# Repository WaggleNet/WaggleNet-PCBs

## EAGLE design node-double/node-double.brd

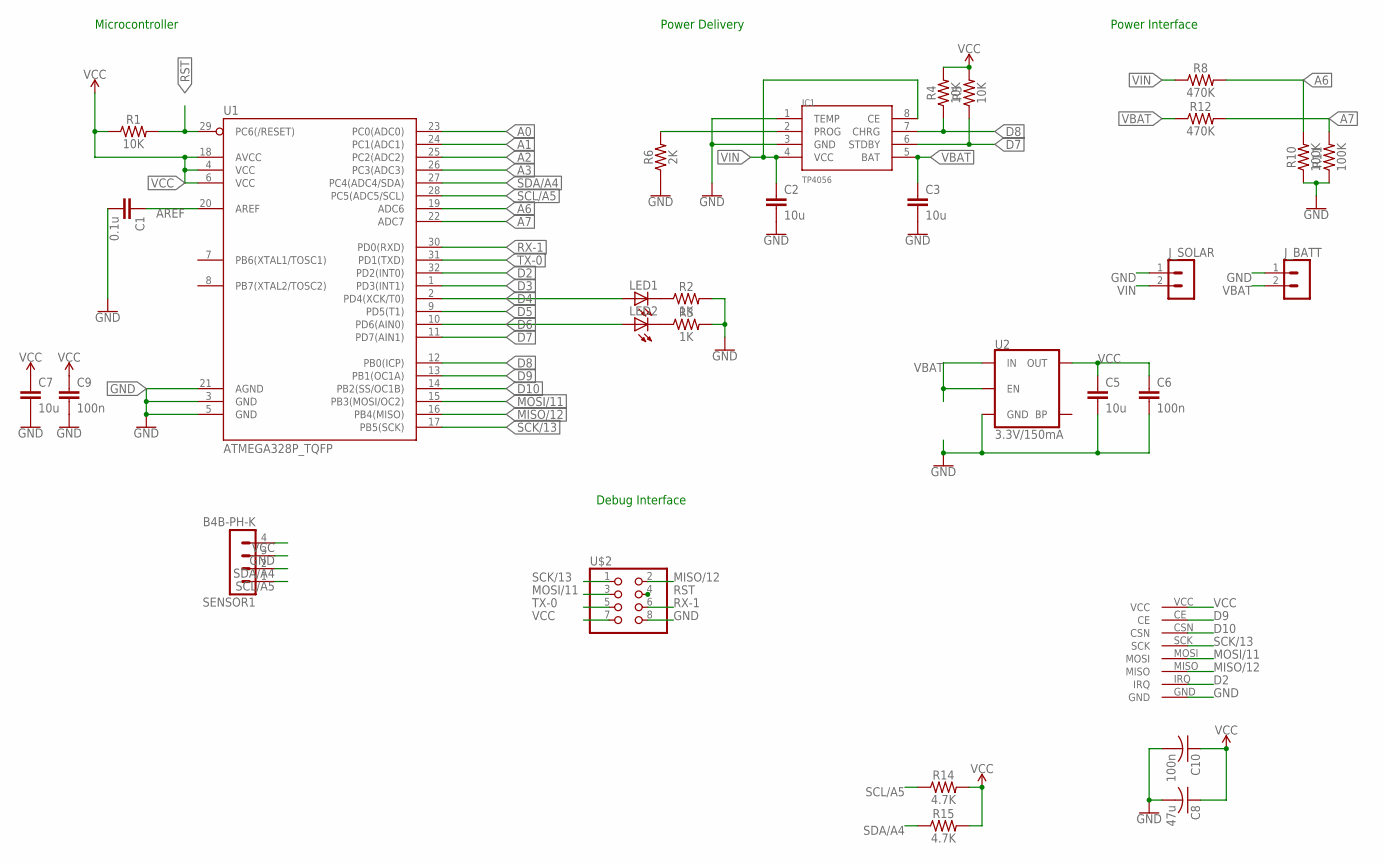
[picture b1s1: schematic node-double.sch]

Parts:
C1: 0.1u; RESC0603_L; MPN CC0603KRX7R7BB104
C2, C3, C5, C7: 10u; RESC0603_L; MPN 08056D106KAT2A
C6, C9: 100n; RESC0603_L; MPN 08056D106KAT2A
C8: 47u; C0603; MPN 08056D106KAT2A
C10: 100n; C0603; MPN 08056D106KAT2A
IC1: TP4056; SOP-8
J_BATT: B2B-PH-K
J_SOLAR: B2B-PH-K
LED1, LED2: LEDSML0805; SML0805
R1, R4, R5: 10K; 0603
R2, R3: 1K; 0603
R6: 2K; 0603; MPN CR0805-JW-222ELF
R8, R12: 470K; 0603; MPN MC01W08051330K
R10, R11: 100K; 0603; MPN CRCW0805100KFKEA
R14, R15: 4.7K; 0603; MPN RC0805JR-074K7L
SENSOR1: B4B-PH-K
U1: ATMEGA328P_TQFP; TQFP32-08; MPN ATMEGA328P-AU
U2: 3.3V/150mA; SOT23-5
U$1: ML01SSMD-SOM; ML01S
U$2: PINHD-2X4; 2X04

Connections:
A0: U1.23 (PC0(ADC0))
A1: U1.24 (PC1(ADC1))
A2: U1.25 (PC2(ADC2))
A3: U1.26 (PC3(ADC3))
A6: R8.2, R10.2, U1.19 (ADC6)
A7: R11.2, R12.2, U1.22 (ADC7)
AREF: C1.1, U1.20 (AREF)
D2: U1.32 (PD2(INT0)), U$1.IRQ
D3: U1.1 (PD3(INT1))
D4: LED1.A, U1.2 (PD4(XCK/T0))
D5: U1.9 (PD5(T1))
D6: LED2.A, U1.10 (PD6(AIN0))
D7: IC1.6 (STDBY), R5.1, U1.11 (PD7(AIN1))
D8: IC1.7 (CHRG), R4.1, U1.12 (PB0(ICP))
D9: U1.13 (PB1(OC1A)), U$1.CE
D10: U1.14 (PB2(SS/OC1B)), U$1.CSN
GND: C1.2, C2.2, C3.2, C5.2, C6.2, C7.2, C8.2, C9.2, C10.2, IC1.1 (TEMP), IC1.3 (GND), J_BATT.1, J_SOLAR.1, R2.2, R3.2, R6.1, R10.1, R11.1, SENSOR1.3, U1.3 (GND), U1.5 (GND), U1.21 (AGND), U2.2 (GND), U$1.GND, U$2.8
MISO/12: U1.16 (PB4(MISO)), U$1.MISO, U$2.2
MOSI/11: U1.15 (PB3(MOSI/OC2)), U$1.MOSI, U$2.3
unnamed: LED1.C, R2.1
unnamed: LED2.C, R3.1
PROG: IC1.2 (PROG), R6.2
RST: R1.2, U1.29 (PC6(/RESET)), U$2.4
RX-1: U1.30 (PD0(RXD)), U$2.6
SCK/13: U1.17 (PB5(SCK)), U$1.SCK, U$2.1
SCL/A5: R14.1, SENSOR1.1, U1.28 (PC5(ADC5/SCL))
SDA/A4: R15.1, SENSOR1.2, U1.27 (PC4(ADC4/SDA))
TX-0: U1.31 (PD1(TXD)), U$2.5
VBAT: C3.1, IC1.5 (BAT), J_BATT.2, R12.1, U2.1 (IN), U2.3 (EN)
VCC: C5.1, C6.1, C7.1, C8.1, C9.1, C10.1, R1.1, R4.2, R5.2, R14.2, R15.2, SENSOR1.4, U1.4 (VCC), U1.6 (VCC), U1.18 (AVCC), U2.5 (OUT), U$1.VCC, U$2.7
VIN: C2.1, IC1.4 (VCC), IC1.8 (CE), J_SOLAR.2, R8.1

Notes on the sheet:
Microcontroller
Power Delivery
Power Interface
Debug Interface

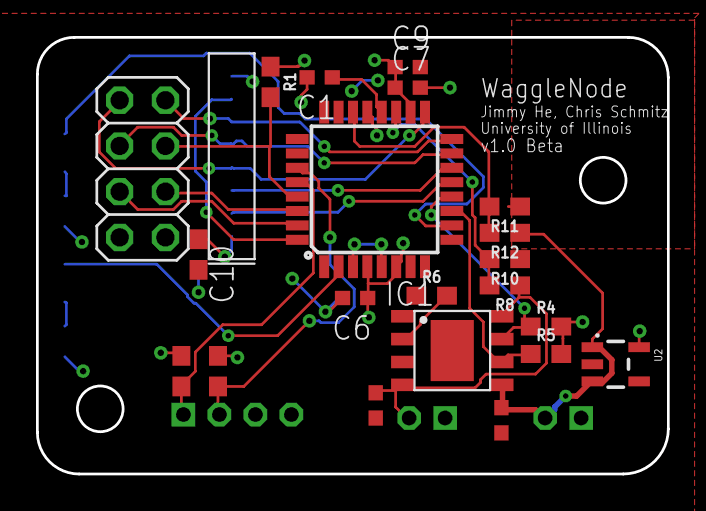
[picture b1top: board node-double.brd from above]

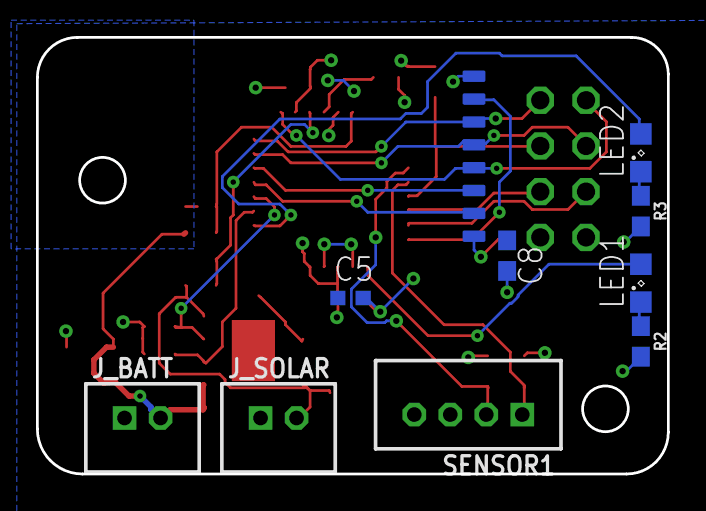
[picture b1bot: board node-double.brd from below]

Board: 2 copper layers, 35.1 x 24.3 mm, 31 parts (10 on the bottom side), 25 nets.

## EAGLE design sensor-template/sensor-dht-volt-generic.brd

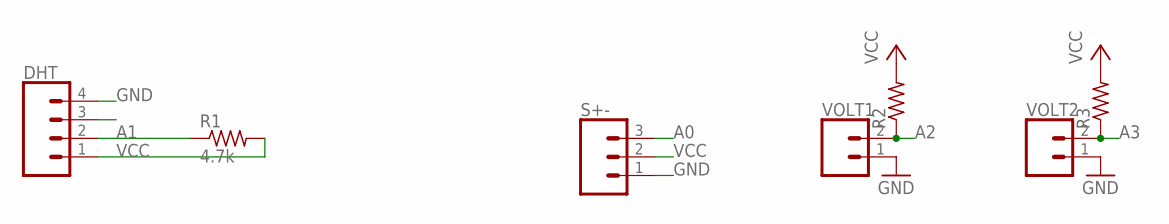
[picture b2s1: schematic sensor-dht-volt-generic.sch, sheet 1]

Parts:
DHT: CONN_04; 1X04
R1: 4.7k; R0603
R2, R3: R-US_R0603; R0603
S+-: CONN_03; 1X03
VOLT1, VOLT2: CONN_02; 1X02

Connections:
A0: S+-.3; also elsewhere on the board
A1: DHT.2, R1.1; also elsewhere on the board
A2: R2.1, VOLT1.2; also elsewhere on the board
A3: R3.1, VOLT2.2; also elsewhere on the board
GND: DHT.4, S+-.1, VOLT1.1, VOLT2.1; also elsewhere on the board
VCC: DHT.1, R1.2, R2.2, R3.2, S+-.2; also elsewhere on the board

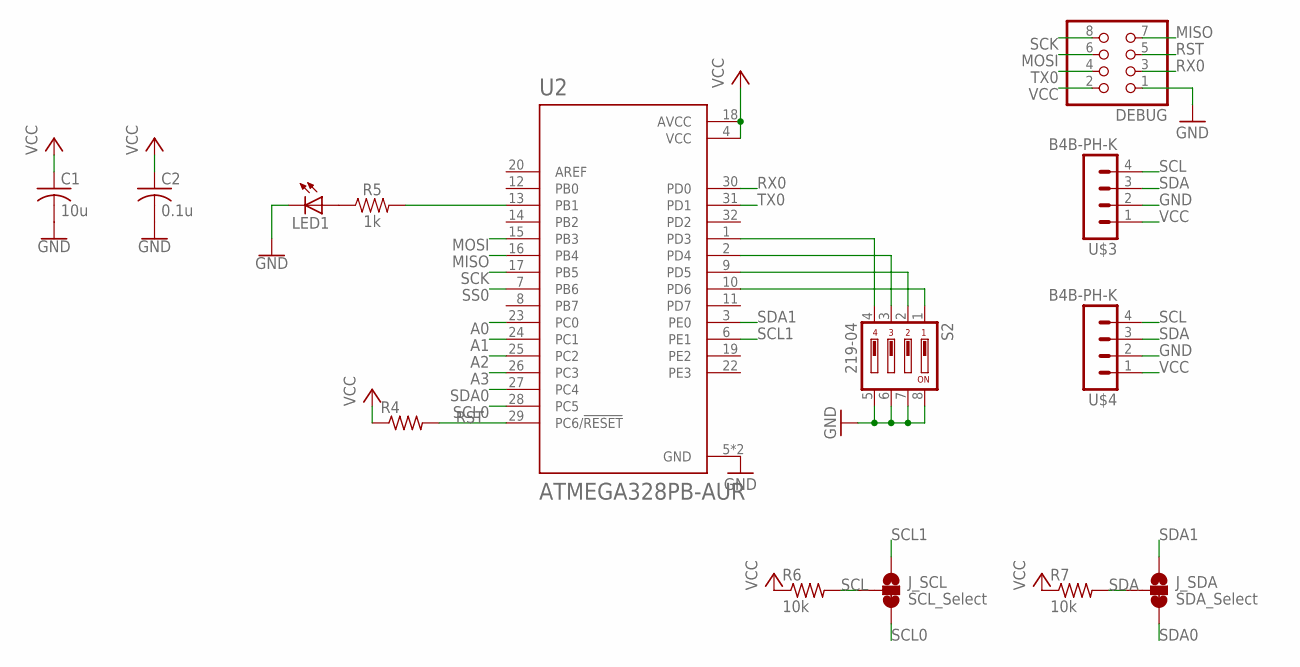
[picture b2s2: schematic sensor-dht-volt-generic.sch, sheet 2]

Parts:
C1: 10u; C0603
C2: 0.1u; C0603
DEBUG: PINHD-2X4; 2X04
J_SCL: SCL_Select; SMT-JUMPER_3_1-NC_TRACE_SILK
J_SDA: SDA_Select; SMT-JUMPER_3_1-NC_TRACE_SILK
LED1: LEDSML0805; SML0805
R4: R-US_R0603; R0603
R5: 1k; 0603
R6, R7: 10k; R0603
S2: 219-04; CTS-219-04
U2: ATMEGA328PB-AUR; QFP80P900X900X120-32N
U$3, U$4: B4B-PH-K

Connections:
A0: U2.23 (PC0); also elsewhere on the board
A1: U2.24 (PC1); also elsewhere on the board
A2: U2.25 (PC2); also elsewhere on the board
A3: U2.26 (PC3); also elsewhere on the board
GND: C1.2, C2.2, DEBUG.1, LED1.C, S2.5, S2.6, S2.7, S2.8, U2.5 (GND), U2.21 (GND), U$3.2, U$4.2; also elsewhere on the board
MISO: DEBUG.7, U2.16 (PB4)
MOSI: DEBUG.6, U2.15 (PB3)
unnamed: S2.4, U2.1 (PD3)
unnamed: S2.3, U2.2 (PD4)
unnamed: S2.2, U2.9 (PD5)
unnamed: S2.1, U2.10 (PD6)
unnamed: LED1.A, R5.1
unnamed: R5.2, U2.13 (PB1)
RST: DEBUG.5, R4.2, U2.29 (PC6/!RESET)
RX0: DEBUG.3, U2.30 (PD0)
SCK: DEBUG.8, U2.17 (PB5)
SCL: J_SCL.2, R6.2, U$3.4, U$4.4
SCL0: J_SCL.3, U2.28 (PC5)
SCL1: J_SCL.1, U2.6 (PE1)
SDA: J_SDA.2, R7.2, U$3.3, U$4.3
SDA0: J_SDA.3, U2.27 (PC4)
SDA1: J_SDA.1, U2.3 (PE0)
SS0: U2.7 (PB6)
TX0: DEBUG.4, U2.31 (PD1)
VCC: C1.1, C2.1, DEBUG.2, R4.1, R6.1, R7.1, U2.4 (VCC), U2.18 (AVCC), U$3.1, U$4.1; also elsewhere on the board

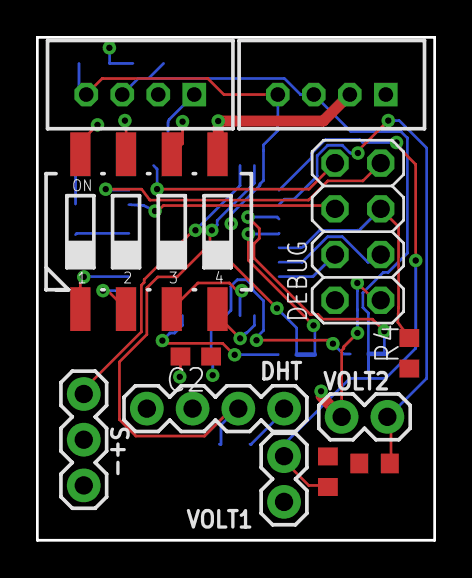
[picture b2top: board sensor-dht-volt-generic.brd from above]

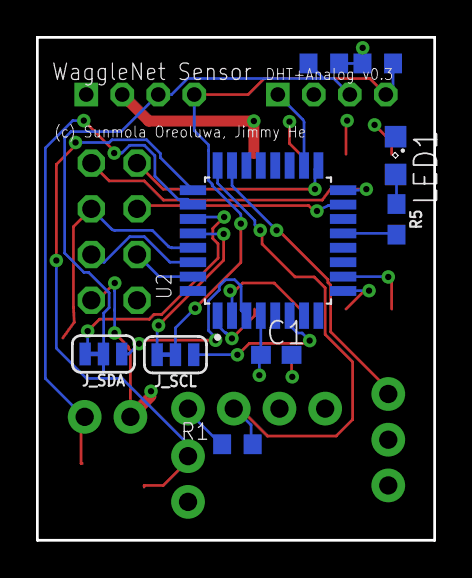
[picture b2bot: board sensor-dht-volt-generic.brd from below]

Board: 2 copper layers, 22.1 x 27.9 mm, 21 parts (9 on the bottom side), 24 nets.

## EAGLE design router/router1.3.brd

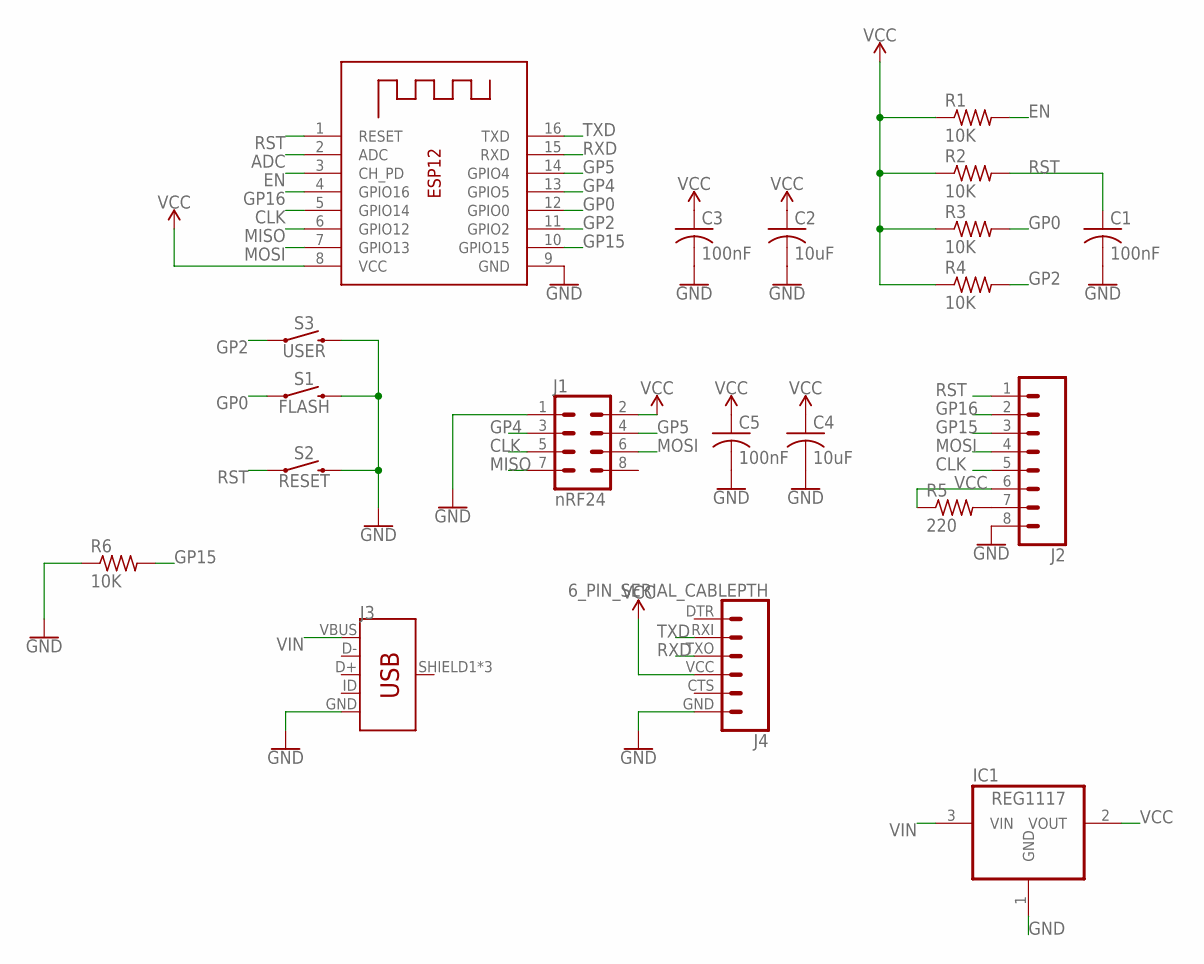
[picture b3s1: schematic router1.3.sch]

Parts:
C1, C3, C5: 100nF; C1206
C2, C4: 10uF; C1206
IC1: REG1117; SOT223
J1: nRF24; 2X4
J2: CONN_08"; 1X08
J3: USB_MICRO-B_FEMALE-SMT; USB-B-MICRO-SMD
J4: 6_PIN_SERIAL_CABLEPTH; FTDI_BASIC
R1, R2, R3, R4, R6: 10K; M1206
R5: 220; M1206
S1: FLASH; TACTILE_SWITCH_PTH_6.0MM
S2: RESET; TACTILE_SWITCH_PTH_6.0MM
S3: USER; TACTILE_SWITCH_PTH_6.0MM
X1: ESP-12

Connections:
ADC: X1.2 (ADC)
CLK: J1.5, J2.5, X1.5 (GPIO14)
EN: R1.2, X1.3 (CH_PD)
GND: C1.2, C2.2, C3.2, C4.2, C5.2, IC1.1 (GND), J1.1, J2.8, J3.GND, J4.GND (6), R6.1, S1.3 (2), S2.3 (2), S3.3 (2), X1.9 (GND)
GP0: R3.2, S1.1, X1.12 (GPIO0)
GP2: R4.2, S3.1, X1.11 (GPIO2)
GP4: J1.3, X1.13 (GPIO5)
GP5: J1.4, X1.14 (GPIO4)
GP15: J2.3, R6.2, X1.10 (GPIO15)
GP16: J2.2, X1.4 (GPIO16)
MISO: J1.7, X1.6 (GPIO12)
MOSI: J1.6, J2.4, X1.7 (GPIO13)
unnamed: J2.7, R5.2
RST: C1.1, J2.1, R2.2, S2.1, X1.1 (RESET)
RXD: J4.TXO (3), X1.15 (RXD)
TXD: J4.RXI (2), X1.16 (TXD)
VCC: C2.1, C3.1, C4.1, C5.1, IC1.2 (VOUT), J1.2, J2.6, J4.VCC (4), R1.1, R2.1, R3.1, R4.1, R5.1, X1.8 (VCC)
VIN: IC1.3 (VIN), J3.VBUS

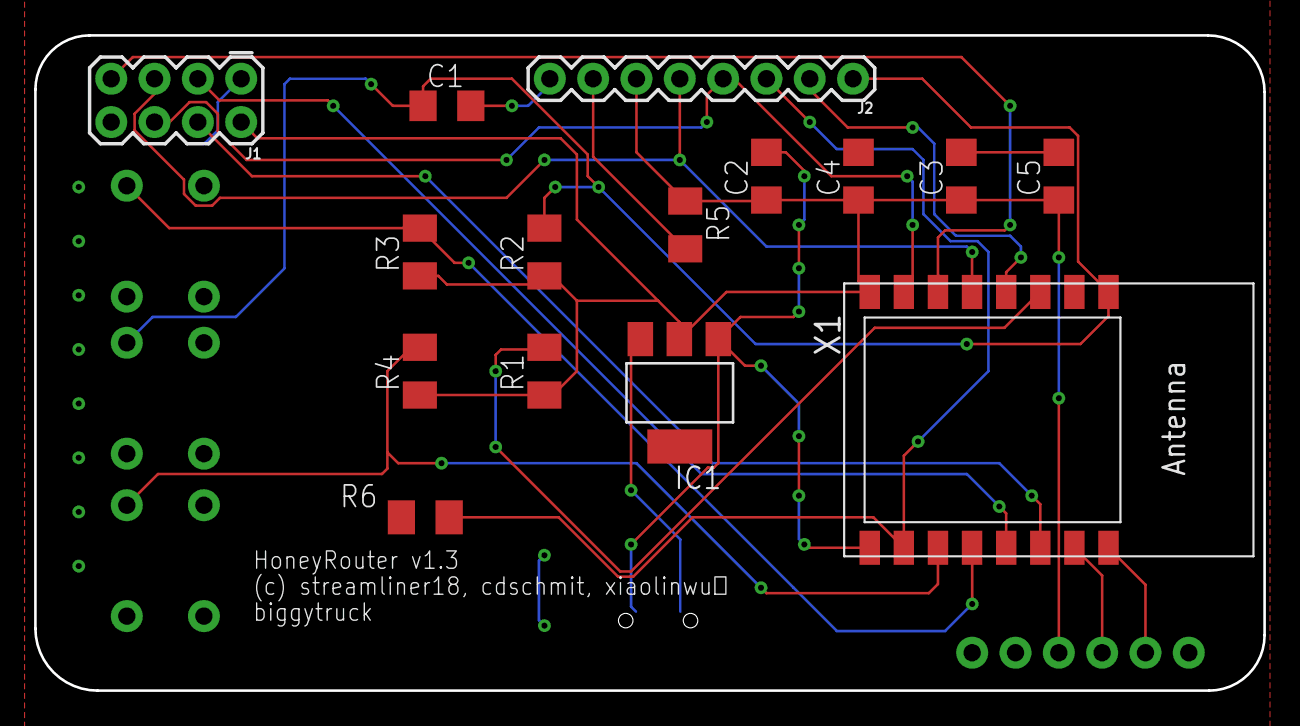
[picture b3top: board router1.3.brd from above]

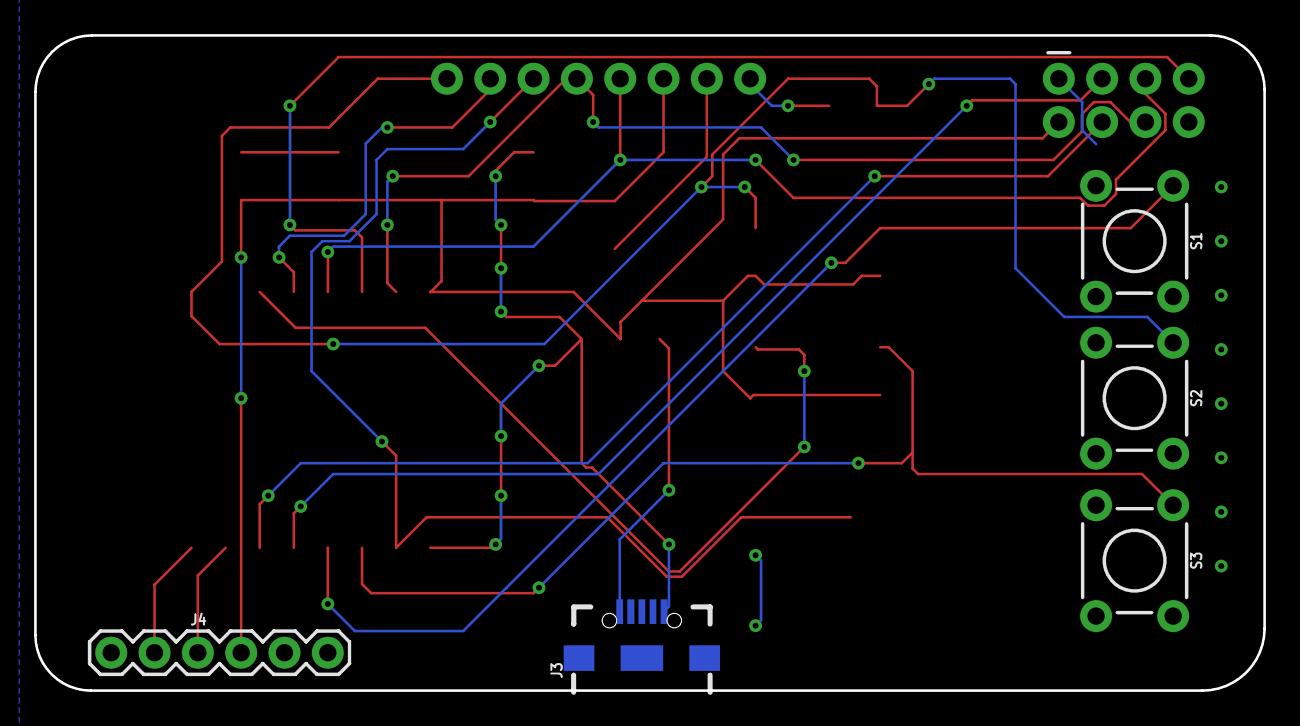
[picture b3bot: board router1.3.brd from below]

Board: 2 copper layers, 72.1 x 38.4 mm, 20 parts (5 on the bottom side), 17 nets.

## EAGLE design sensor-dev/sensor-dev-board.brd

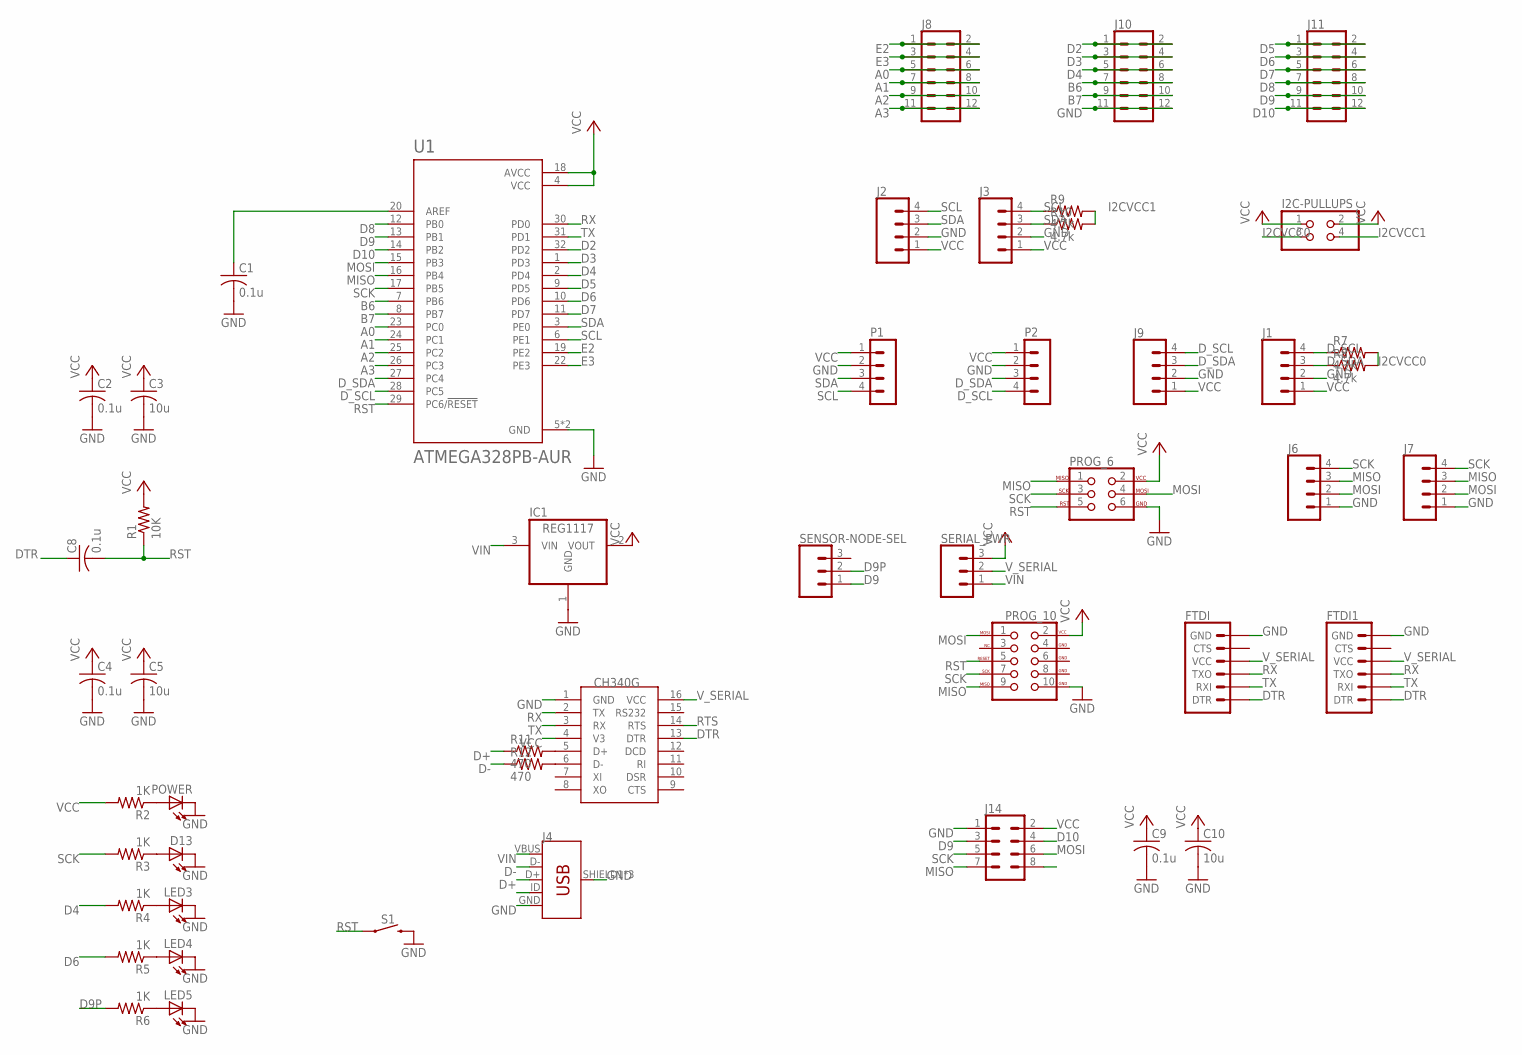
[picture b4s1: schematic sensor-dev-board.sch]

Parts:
C1, C2, C4, C8, C9: 0.1u; C1206
C3, C5, C10: 10u; C1206
CH340C: CH340C; SOIC16
D13: LEDSML1206; SML1206
FTDI, FTDI1: 6_PIN_SERIAL_TARGET; 1X06
I2C-PULLUPS: PINHD-2X2; 2X02
IC1: REG1117; SOT223
J1, J2, J3, J6, J7, J9: CONN_04; 1X04
J4: USB_MICRO-B_FEMALE-SMT; USB-B-MICRO-SMD
J8, J10, J11: CONN_06X2PTH_FEMALE; 2X6
J14: CONN_04X2; 2X4
LED3, LED4, LED5: LEDSML1206; SML1206
P1, P2: B4B-PH-K
POWER: LEDSML1206; SML1206
PROG_6: AVR_SPI_PROG_3X2PTH; 2X3
PROG_10: AVR_SPI_PROG_5X2PTH; 2X5
R1: 10K; R1206
R2, R3, R4, R5, R6: 1K; R1206
R7, R8, R9, R10: 4.7k; R1206
R11, R12: 470; R1206
S1: MOMENTARY-SWITCH-SPST-PTH-6.0MM; TACTILE_SWITCH_PTH_6.0MM
SENSOR-NODE-SEL: CONN_03; 1X03
SERIAL_PWR: CONN_03; 1X03
U1: ATMEGA328PB-AUR; QFP80P900X900X120-32N

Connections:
A0: J8.5, J8.6, U1.23 (PC0)
A1: J8.7, J8.8, U1.24 (PC1)
A2: J8.9, J8.10, U1.25 (PC2)
A3: J8.11, J8.12, U1.26 (PC3)
B6: J10.7, J10.8, U1.7 (PB6)
B7: J10.9, J10.10, U1.8 (PB7)
D2: J10.1, J10.2, U1.32 (PD2)
D3: J10.3, J10.4, U1.1 (PD3)
D4: J10.5, J10.6, R4.2, U1.2 (PD4)
D5: J11.1, J11.2, U1.9 (PD5)
D6: J11.3, J11.4, R5.2, U1.10 (PD6)
D7: J11.5, J11.6, U1.11 (PD7)
D8: J11.7, J11.8, U1.12 (PB0)
D9: J11.9, J11.10, J14.3, SENSOR-NODE-SEL.1, U1.13 (PB1)
D9P: R6.2, SENSOR-NODE-SEL.2
D10: J11.11, J11.12, J14.4, U1.14 (PB2)
D+: J4.D+, R11.1
D-: J4.D-, R12.1
DTR: C8.1, CH340C.13 (DTR), FTDI.1 (DTR), FTDI1.1 (DTR)
D_SCL: J1.4, J9.4, P2.4, R7.1, U1.28 (PC5)
D_SDA: J1.3, J9.3, P2.3, R8.1, U1.27 (PC4)
E2: J8.1, J8.2, U1.19 (PE2)
E3: J8.3, J8.4, U1.22 (PE3)
GND: C1.2, C2.2, C3.2, C4.2, C5.2, C9.2, C10.2, CH340C.1 (GND), D13.C, FTDI.6 (GND), FTDI1.6 (GND), IC1.1 (GND), J1.2, J2.2, J3.2, J4.GND, J4.SHIELD1 (SHIELD), J4.SHIELD2 (SHIELD), J4.SHIELD3 (SHIELD), J6.1, J7.1, J9.2, J10.11, J10.12, J14.1, LED3.C, LED4.C, LED5.C, P1.2, P2.2, POWER.C, PROG_6.6, PROG_10.4 (GND), PROG_10.6 (GND), PROG_10.8 (GND), PROG_10.10 (GND), S1.3 (2), U1.5 (GND), U1.21 (GND)
I2CVCC0: I2C-PULLUPS.3, R7.2, R8.2
I2CVCC1: I2C-PULLUPS.4, R9.2, R10.2
MISO: J6.3, J7.3, J14.7, PROG_6.1, PROG_10.9 (MISO), U1.16 (PB4)
MOSI: J6.2, J7.2, J14.6, PROG_6.4, PROG_10.1 (MOSI), U1.15 (PB3)
unnamed: CH340C.5 (D+), R11.2
unnamed: CH340C.6 (D-), R12.2
unnamed: C1.1, U1.20 (AREF)
unnamed: POWER.A, R2.1
unnamed: D13.A, R3.1
unnamed: LED3.A, R4.1
unnamed: LED4.A, R5.1
unnamed: LED5.A, R6.1
RST: C8.2, PROG_6.5, PROG_10.5 (RESET), R1.1, S1.1, U1.29 (PC6/!RESET)
RTS: CH340C.14 (RTS)
RX: CH340C.2 (TX), FTDI.3 (TXO), FTDI1.3 (TXO), U1.30 (PD0)
SCK: J6.4, J7.4, J14.5, PROG_6.3, PROG_10.7 (SCK), R3.2, U1.17 (PB5)
SCL: J2.4, J3.4, P1.4, R9.1, U1.6 (PE1)
SDA: J2.3, J3.3, P1.3, R10.1, U1.3 (PE0)
TX: CH340C.3 (RX), FTDI.2 (RXI), FTDI1.2 (RXI), U1.31 (PD1)
VCC: C2.1, C3.1, C4.1, C5.1, C9.1, C10.1, CH340C.4 (V3), I2C-PULLUPS.1, I2C-PULLUPS.2, IC1.2 (VOUT), J1.1, J2.1, J3.1, J9.1, J14.2, P1.1, P2.1, PROG_6.2, PROG_10.2 (VCC), R1.2, R2.2, SERIAL_PWR.3, U1.4 (VCC), U1.18 (AVCC)
VIN: IC1.3 (VIN), J4.VBUS, SERIAL_PWR.1
V_SERIAL: CH340C.16 (VCC), FTDI.4 (VCC), FTDI1.4 (VCC), SERIAL_PWR.2

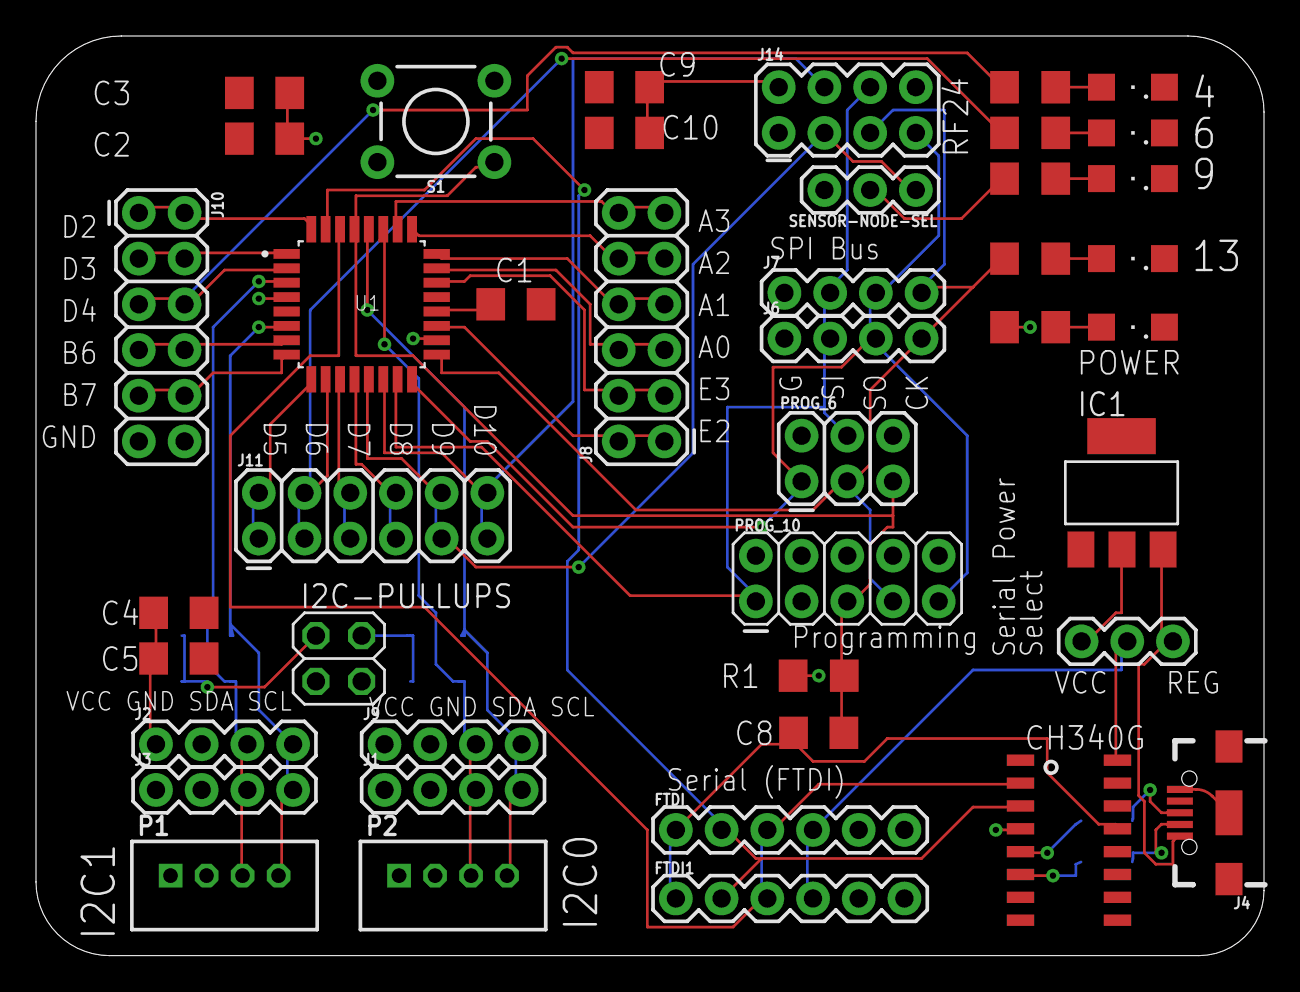
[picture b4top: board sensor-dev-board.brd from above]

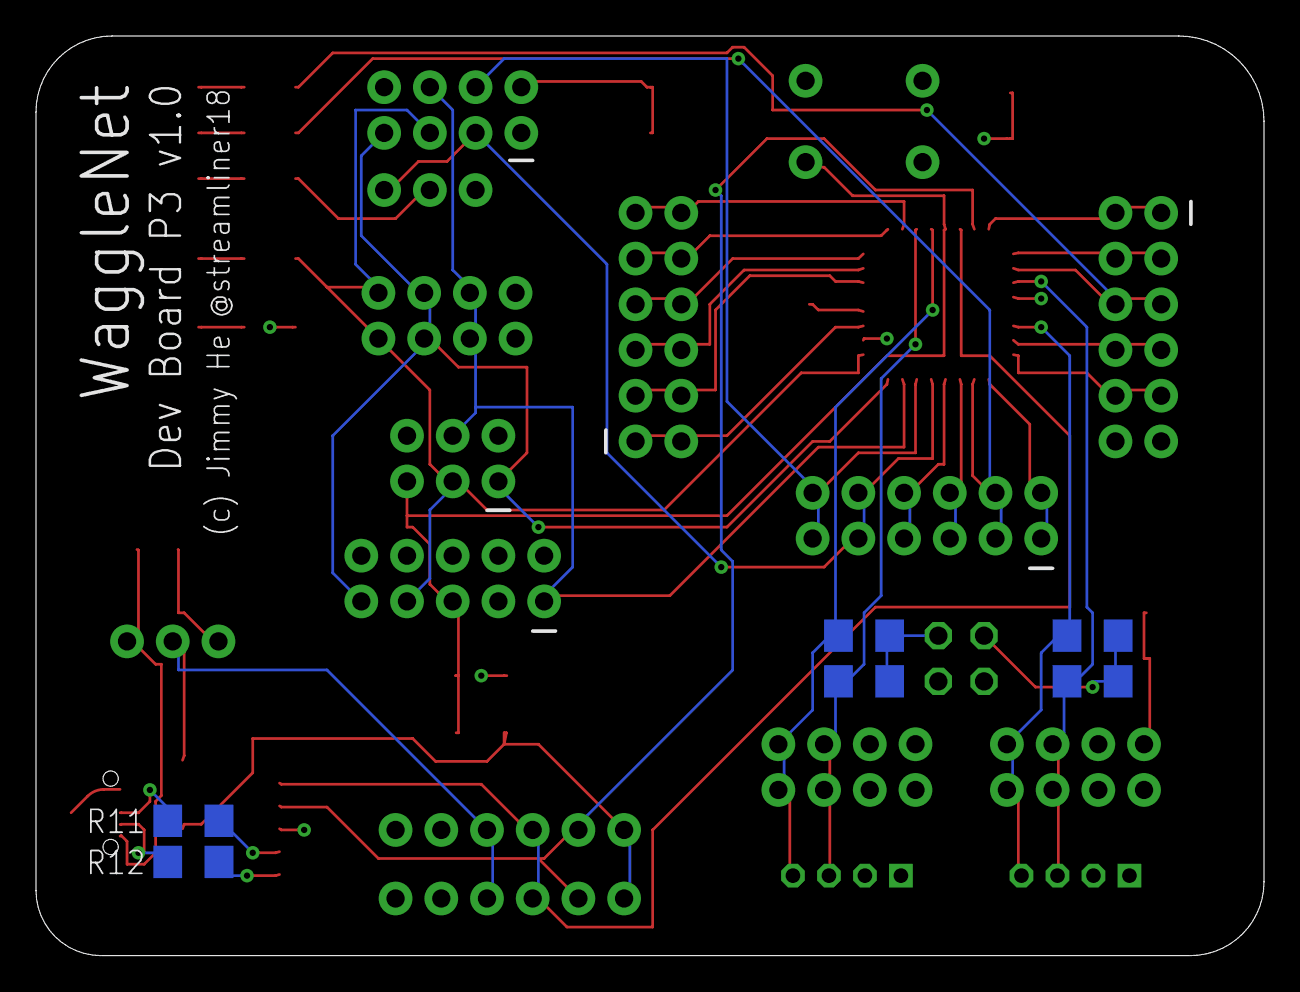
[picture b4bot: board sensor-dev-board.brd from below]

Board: 2 copper layers, 68.2 x 51.1 mm, 49 parts (6 on the bottom side), 45 nets.

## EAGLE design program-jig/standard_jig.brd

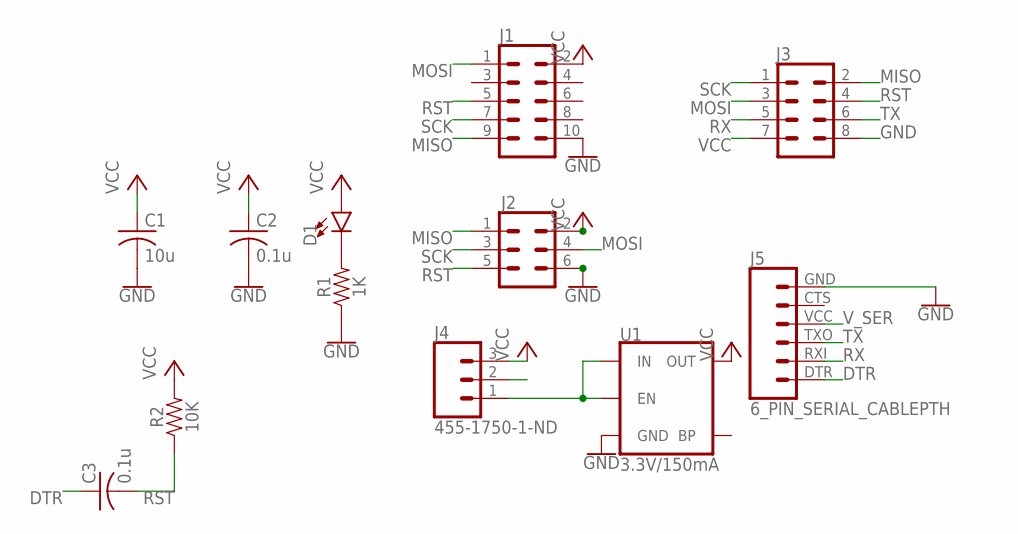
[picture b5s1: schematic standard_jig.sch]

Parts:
C1: 10u; C1206
C2, C3: 0.1u; C1206
D1: LED1206; LED-1206
J1: CONN_05X2SHD; 2X5-SHROUDED
J2: CONN_03X2SHROUD; 2X3-SHROUDED
J3: CONN_04X2; 2X4
J4: 455-1750-1-ND; 1X03
J5: 6_PIN_SERIAL_CABLEPTH; FTDI_BASIC
R1: 1K; 1206
R2: 10K; 1206
U1: 3.3V/150mA; SOT23-5

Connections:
DTR: C3.1, J5.DTR (1)
GND: C1.2, C2.2, J1.10, J2.6, J3.8, J5.GND (6), R1.1, U1.2 (GND)
MISO: J1.9, J2.1, J3.2
MOSI: J1.1, J2.4, J3.3
unnamed: D1.C, R1.2
unnamed: J4.1, U1.1 (IN), U1.3 (EN)
RST: C3.2, J1.5, J2.5, J3.4, R2.1
RX: J3.5, J5.RXI (2)
SCK: J1.7, J2.3, J3.1
TX: J3.6, J5.TXO (3)
VCC: C1.1, C2.1, D1.A, J1.2, J2.2, J3.7, J4.3, R2.2, U1.5 (OUT)
V_SER: J5.VCC (4)

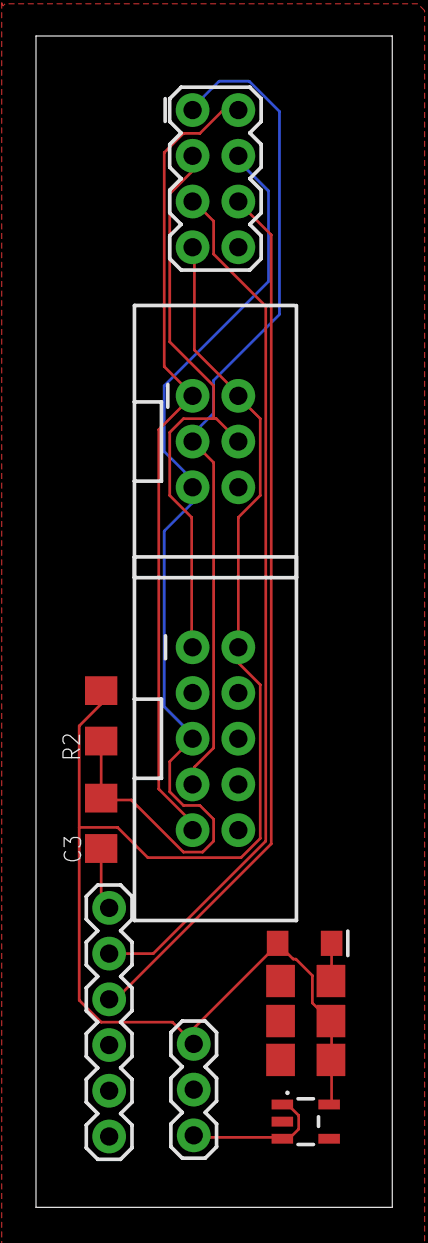
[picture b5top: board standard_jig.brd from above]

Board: 2 copper layers, 19.8 x 65.1 mm, 12 parts (0 on the bottom side), 11 nets.

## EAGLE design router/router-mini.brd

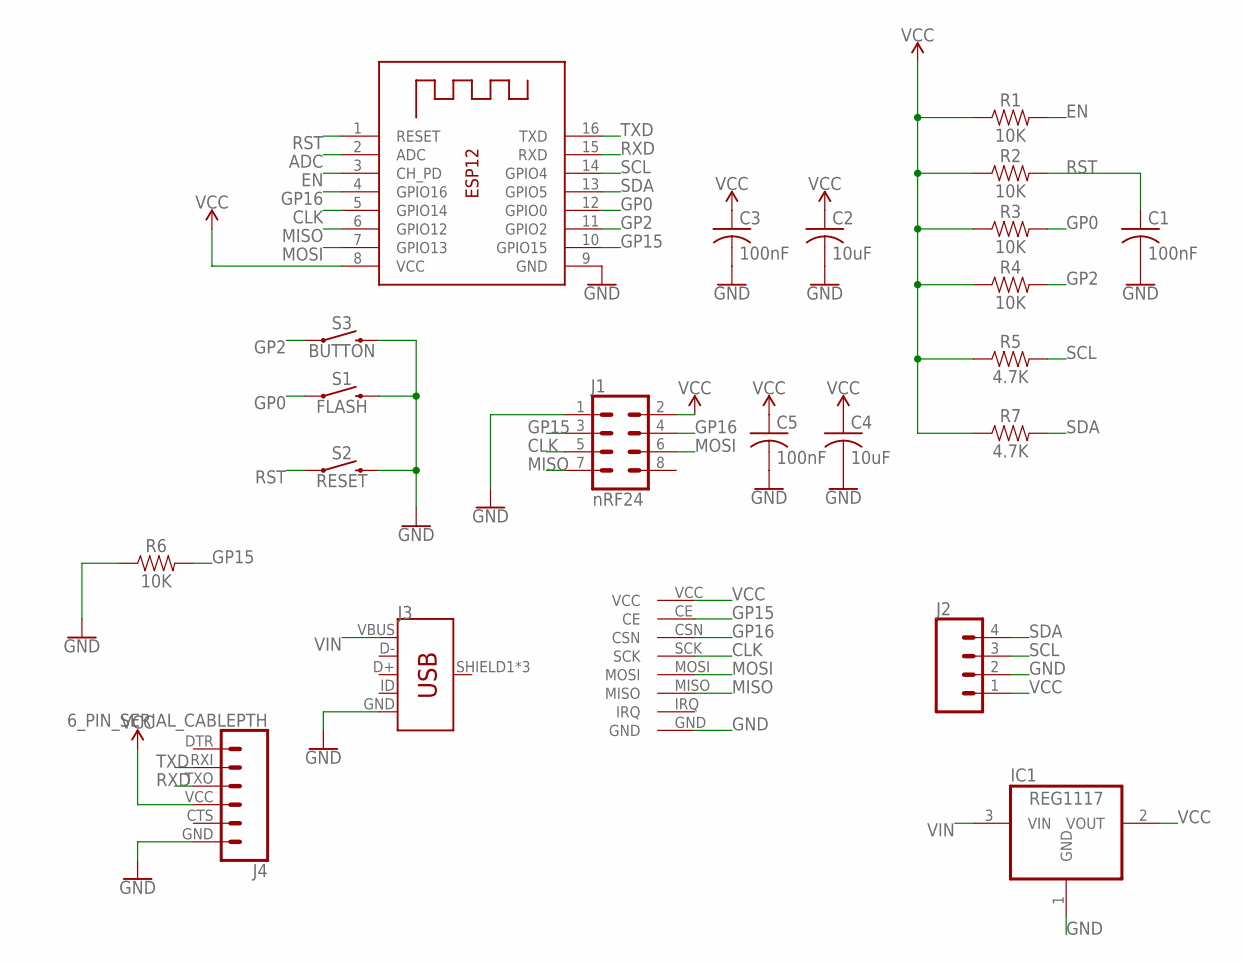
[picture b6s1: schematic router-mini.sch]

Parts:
C1, C3, C5: 100nF; C1206
C2, C4: 10uF; C1206
IC1: REG1117; SOT223
J1: nRF24; 2X4
J2: CONN_04; 1X04
J3: USB_MICRO-B_FEMALE-SMT; USB-B-MICRO-SMD
J4: 6_PIN_SERIAL_CABLEPTH; FTDI_BASIC
R1, R2, R3, R4, R6: 10K; 1206
R5, R7: 4.7K; 1206
S1: FLASH; TACTILE_SWITCH_SMD_5.2MM
S2: RESET; TACTILE_SWITCH_SMD_5.2MM
S3: BUTTON; TACTILE_SWITCH_SMD_5.2MM
U$1: ML01SSMD-SOM; ML01S
X1: ESP-12

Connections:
ADC: X1.2 (ADC)
CLK: J1.5, U$1.SCK, X1.5 (GPIO14)
EN: R1.2, X1.3 (CH_PD)
GND: C1.2, C2.2, C3.2, C4.2, C5.2, IC1.1 (GND), J1.1, J2.2, J3.GND, J4.GND (6), R6.1, S1.3 (2), S1.4 (2), S2.3 (2), S2.4 (2), S3.3 (2), S3.4 (2), U$1.GND, X1.9 (GND)
GP0: R3.2, S1.1, S1.2 (1), X1.12 (GPIO0)
GP2: R4.2, S3.1, S3.2 (1), X1.11 (GPIO2)
GP15: J1.3, R6.2, U$1.CE, X1.10 (GPIO15)
GP16: J1.4, U$1.CSN, X1.4 (GPIO16)
MISO: J1.7, U$1.MISO, X1.6 (GPIO12)
MOSI: J1.6, U$1.MOSI, X1.7 (GPIO13)
RST: C1.1, R2.2, S2.1, S2.2 (1), X1.1 (RESET)
RXD: J4.TXO (3), X1.15 (RXD)
SCL: J2.3, R5.2, X1.14 (GPIO4)
SDA: J2.4, R7.2, X1.13 (GPIO5)
TXD: J4.RXI (2), X1.16 (TXD)
VCC: C2.1, C3.1, C4.1, C5.1, IC1.2 (VOUT), J1.2, J2.1, J4.VCC (4), R1.1, R2.1, R3.1, R4.1, R5.1, R7.1, U$1.VCC, X1.8 (VCC)
VIN: IC1.3 (VIN), J3.VBUS

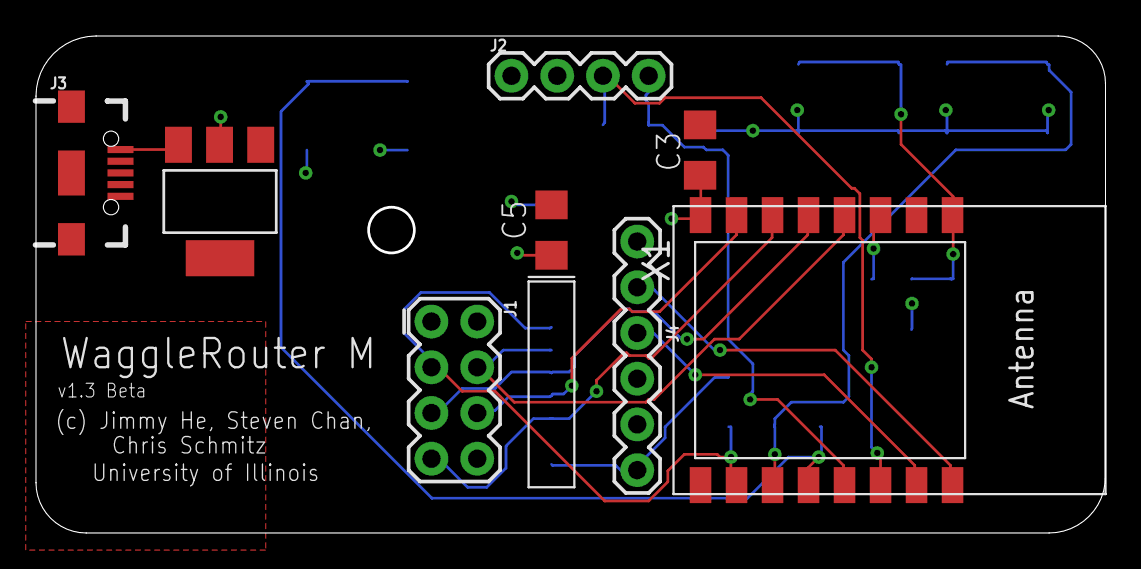
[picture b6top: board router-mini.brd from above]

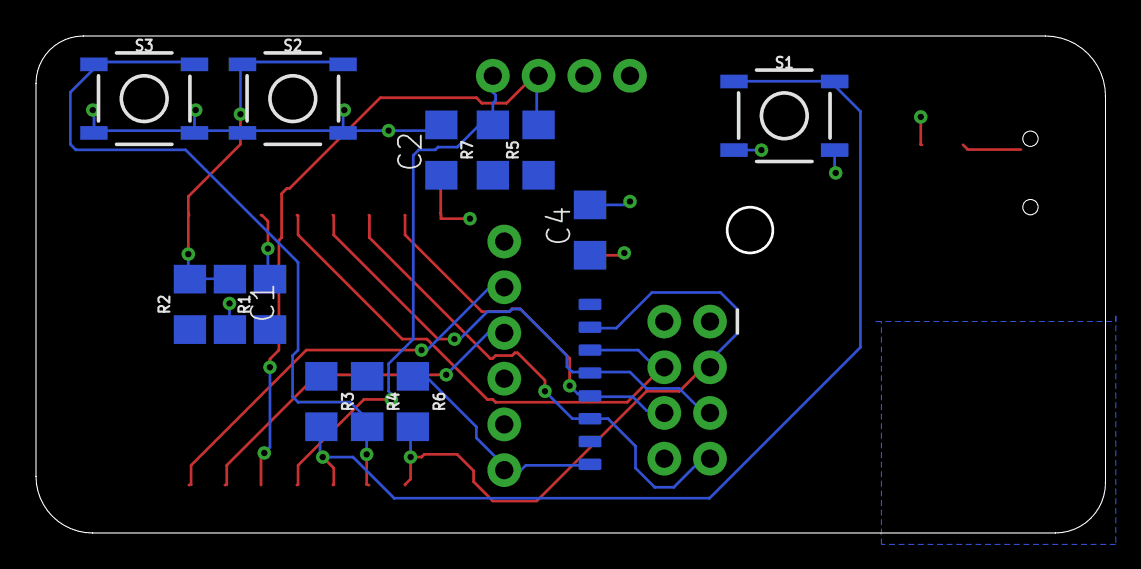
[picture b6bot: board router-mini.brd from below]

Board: 2 copper layers, 59.3 x 27.5 mm, 22 parts (14 on the bottom side), 16 nets.

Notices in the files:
parts and their libraries:
SparkFun-Connectors: Licensing: Creative Commons ShareAlike 4.0 International - https://creativecommons.org/licenses/by-sa/4.0
con-jst-ph: Copyright (C) 2016, Bob Starr
